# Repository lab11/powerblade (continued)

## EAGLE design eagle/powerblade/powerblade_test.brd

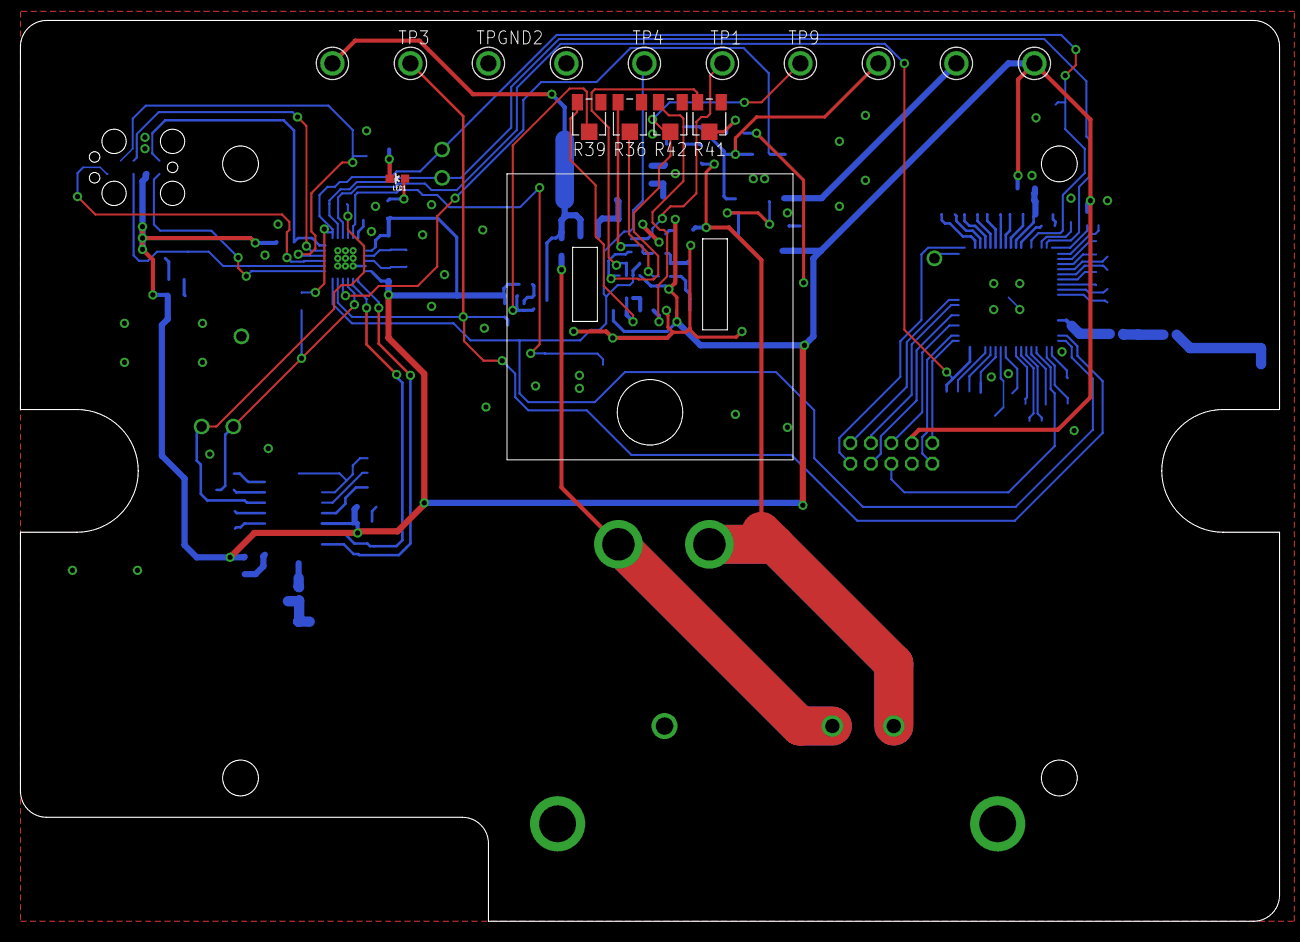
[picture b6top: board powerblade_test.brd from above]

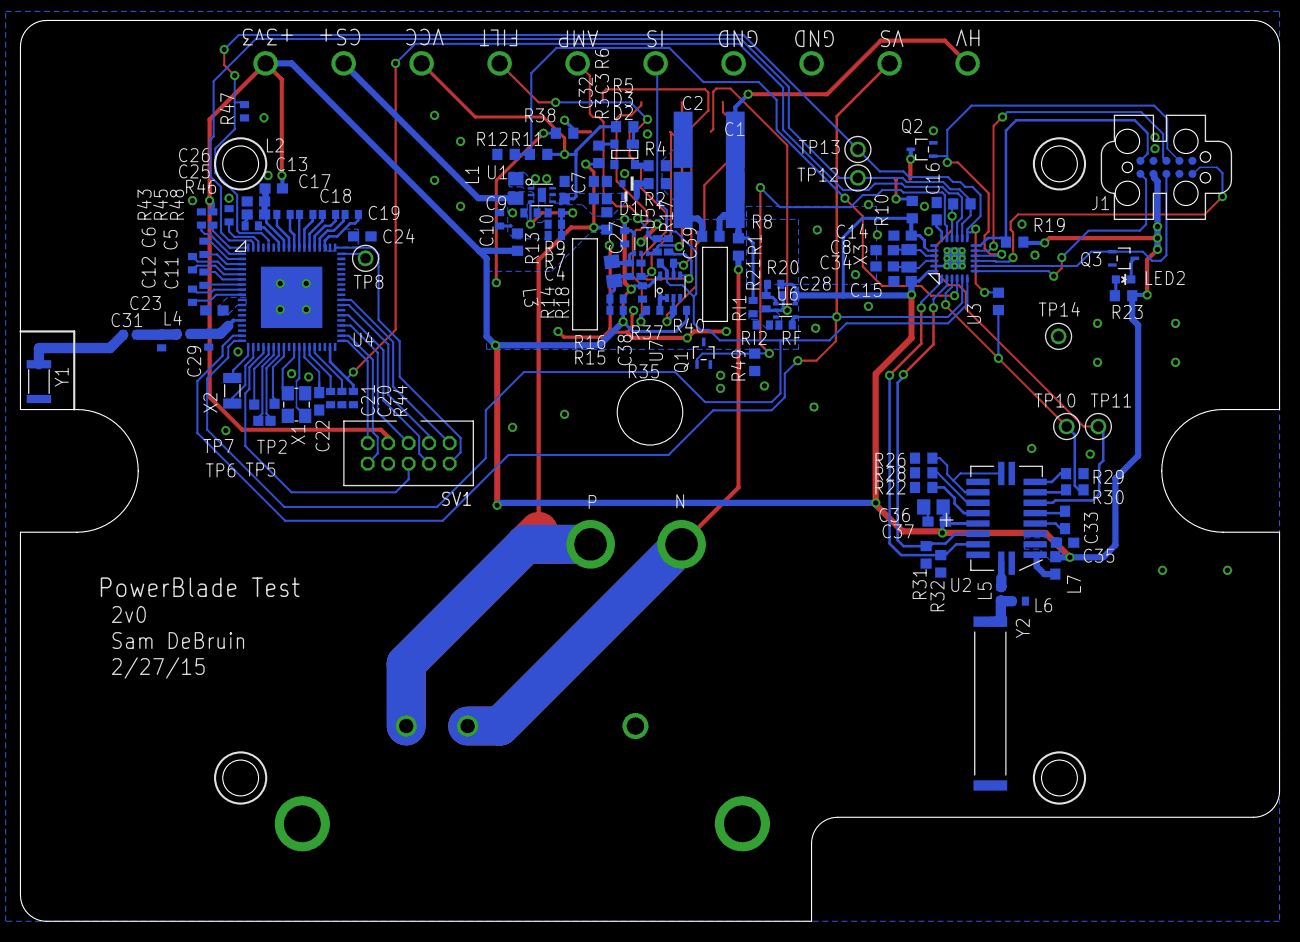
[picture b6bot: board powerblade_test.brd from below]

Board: 2 copper layers, 123.0 x 88.0 mm, 139 parts (123 on the bottom side), 108 nets.

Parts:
ACSLOT: AC_NODIM; AC3_NODIM
C1: 0.033uF 250VAC; C2220K
C2: NP; C2220K
C3, C32: 33uF; C0603
C4: 22pF; C0402
C5, C6, C11, C12, C13, C17, C18, C19, C20, C21: 56nF; C0402
C7: 4.7uF; C0603
C8, C34: 8pF; C0603
C9, C27, C28, C38: 0.1uF; C0402
C10: 4.7uF; C0402
C14, C22, C25: 0.1uF; C0603
C15: 10uF; C0603
C16: 470nF; C0603
C23: 0.47uF; C0603
C24: 0.22uF; C0603
C26: 2.2uF; C0603
C29: 1.2pF; C0402
C30: NP; C0402
C31: 0ohm; C0402
C33: 15nF; C0603
C35: 27pF; C0603
C36: 100pF; C0603
C37: 4.7uF; CPOL-0805
C39: 1.5uF; C0402
CS+: TP_MULT
CS-: TP_MULT
D1: ZENERBZT52; BZT52
D2: DIODE; BAS521
D3: BRIDGE_BGX; TO-253-4
HVS: TP_MULT
J1: JTAG_14PIN_IDC; TC2050-IDC-430
J21: AC_INSW; AC_DC21
L1: 10uH; L0805
L2: 2.2uH; L0603
L3: L0805
L4: 7.5nH; L0402
L5: 10nH; L0402
L6: 100nH; L0402
L7: 100nH; L0603
LED1, LED2: LED-0603
Q1, Q2, Q3: 2SK1829; SC-70-3
R1: 240 0.25W; R0603
R2, R3: 0; R0603
R4, R5, R6, R33, R34: NP; R0603
R7: 560k; R0402
R8: 1M; R0603
R9: 180k; R0402
R10, R23: 120; R0603
R11: 134k 1%; R0603
R12: 67k 1%; R0603
R13: 1 1%; R0603
R14: 200; R0402
R15: NP; R0402
R16, R43: 0; R0402
R17: 20k 1%; R0402
R18: 2.49 1%; R0402
R19, R31, R32, R49: 47k; R0603
R20, R21: 10k 1%; R0402
R22: 270k; R0603
R26, R29: 100k; R0603
R28: 330k; R0603
R30: 4.7k; R0603
R35: 2k 1%; R0402
R36: 20; 3313_POT
R37: 90k 1%; R0402
R38: 3.1k 1%; R0603
R39, R41: 10k; 3313_POT
R40: 100k 1%; R0402
R42: 50k; 3313_POT
R44, R46, R48: 47k; R0402
R45, R47: 12k; R0402
RF: 1.5k 1%; R0402
RI1, RI2: 220k 1%; R0402
RS+: TP_MULT
SV1: MA05-2_KEY
TP1, TP3, TP4, TP9: TP_MULT
TP2, TP5, TP6, TP7: TP_SMD
TP8, TP10, TP11, TP12, TP13, TP14: TP_STD; TP
TPGND1, TPGND2: TP_MULT
U1: TPS62122; WDFN-6
U2: TR1000; SM-20H
U3: MSP430FR5738; VQFN-24
U4: LTC5800; QFN-72
U5, U6: MAX9910; SC70-5
U7: OPA2369; SOT-23-8
X1: ABM8G
X2: ABS07
X3: 32.768kHz; 0805
Y1: UREACH_XTEND
Y2: ANT-916

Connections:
+3V3: C14.1, C15.1, C27.1, C28.1, C35.1, C36.1, C37.+, C38.1, CS-.P$1, J1.P2, L2.1, L7.1, R10.2, R13.2, R15.1, R19.2, R20.2, R23.2, R40.2, R45.2, SV1.7, U2.P3, U2.P16, U3.P20, U3.P24, U5.P5, U6.P5, U7.P8
CNT0: R32.2, U2.P18, U3.P1
CNT1: R31.2, U2.P17, U3.P2
DGND: C27.2, C28.2, C38.2, Q1.P3, R16.1, R18.1, R21.1, R38.1, R39.PW, RI2.1, U5.P2, U6.P2, U7.P4
FLASH_EN: SV1.2, U4.P55
GND: C3.2, C7.2, C8.1, C9.2, C10.2, C14.2, C15.2, C16.1, C20.2, C21.2, C22.2, C23.2, C24.2, C25.2, C26.2, C29.2, C30.2, C32.2, C34.1, C35.2, C36.2, C37.-, D2.A, D3.P3, J1.P9, L6.2, Q1.P2, Q2.P2, Q3.P2, R9.1, R12.1, R22.1, R26.2, R28.1, R29.1, R31.1, R32.1, R43.2, R44.1, R46.1, R47.1, R48.1, R49.1, SV1.8, TP14.P$1, TPGND1.P$1, TPGND2.P$1, U1.P6, U1.PAD, U2.P1, U2.P10, U2.P19, U3.G1, U3.G2, U3.G3, U3.G4, U3.G5, U3.G6, U3.G7, U3.G8, U3.G9, U3.P19, U3.P23, U3.PAD, U4.PAD, X1.P2, X1.P4
IPC_MISO: SV1.5, U4.P40
IPC_MOSI: SV1.4, U4.P42
IPC_SCK: SV1.3, U4.P44
IPC_SS: SV1.1, U4.P45
I_SENSE: R37.2, TP4.P$1, U3.P6, U4.P18, U7.P7
LTC_RRTS: R46.2, U4.P66
LTC_RX: R33.1, R47.2, TP13.P$1, U3.P13, U4.P68
LTC_SLEEP: R44.2, U3.P15, U4.P35
LTC_TCTS: R48.2, U4.P70
LTC_TIME: R45.1, U4.P72
LTC_TX: R34.1, TP12.P$1, U3.P14, U4.P71
METER_EN: Q1.P1, R49.2, U3.P17
N: J21.N, R1.1
unnamed: C34.2, U3.P22, X3.1
unnamed: D1.A, D2.C, R2.2
unnamed: C1.1, C2.1, R2.1, R4.1, R8.2
unnamed: D3.P4, R4.2
unnamed: D3.P1, R5.1
unnamed: D3.P2, R6.2
unnamed: L1.2, U1.P1
unnamed: C5.1, U4.P2
unnamed: C4.1, C9.1, C10.1, CS+.P$1, L1.1, R7.2, R13.1, U1.P2
unnamed: C33.2, U2.P5
unnamed: C4.2, R7.1, R9.2, U1.P3
unnamed: C5.2, U4.P3
unnamed: C6.1, U4.P5
unnamed: L7.2, U2.P2
unnamed: C6.2, U4.P4
unnamed: C11.1, U4.P6
unnamed: C11.2, U4.P7
unnamed: C12.1, U4.P9
unnamed: C12.2, U4.P8
unnamed: C13.1, U4.P64
unnamed: C16.2, U3.P18
unnamed: C13.2, U4.P63
unnamed: C17.1, U4.P61
unnamed: C17.2, U4.P62
unnamed: C18.1, U4.P60
unnamed: C18.2, U4.P59
unnamed: C19.1, U4.P57
unnamed: C19.2, U4.P58
unnamed: C21.1, U4.P31
unnamed: C20.1, U4.P32
unnamed: C25.1, C26.1, L2.2, U4.P65
unnamed: C24.1, U4.P56
unnamed: C23.1, U4.P10
unnamed: C22.1, U4.P30
unnamed: L3.2, R14.1, R15.2, R16.2
unnamed: L3.1, R14.2, U5.P1
unnamed: R17.1, R36.P2, U5.P3
unnamed: R20.1, R21.2, U6.P1
unnamed: RF.1, RI1.2, RI2.2, U6.P3
unnamed: U4.P29, X1.P1
unnamed: U4.P28, X1.P3
unnamed: U4.P20, X2.P2
unnamed: U4.P19, X2.P1
unnamed: C29.1, L4.2, U4.P14
unnamed: C30.1, C31.1, L4.1
unnamed: C31.2, Y1.P1
unnamed: LED1.A, R10.1
unnamed: R22.2, U2.P15
unnamed: R28.2, U2.P14
unnamed: R29.2, U2.P9
unnamed: R30.2, U2.P8
unnamed: LED1.C, Q2.P3
unnamed: C33.1, U2.P6
unnamed: C8.2, U3.P21, X3.2
unnamed: R26.1, U2.P11, U2.P13
unnamed: LED2.A, R23.1
unnamed: LED2.C, Q3.P3
unnamed: TP8.P$1, U4.P54
unnamed: C39.1, R17.2, TP1.P$1, U5.P4
unnamed: L5.2, U2.P20
unnamed: L5.1, L6.1, Y2.P1
unnamed: R18.2, R36.PW
unnamed: R37.1, R41.P2, U7.P6
unnamed: C39.2, R42.PW, TP9.P$1, U7.P5
unnamed: R35.1, U7.P1, U7.P2
unnamed: R38.2, R41.PW
unnamed: R39.P2, R40.1, U7.P3
unnamed: R35.2, R42.P2
unnamed: TP7.P$1, U4.P23
unnamed: TP6.P$1, U4.P24
unnamed: TP5.P$1, U4.P25
unnamed: TP2.P$1, U4.P26
unnamed: R43.1, U4.P1
NRST: SV1.6, U4.P22
P: J21.L, R3.1, R6.1
RST: J1.P10, R19.1, U3.P12
RXDATA: R34.2, TP11.P$1, U2.P7, U3.P16
TCK: J1.P7, Q2.P1, U3.P10
TDI: J1.P3, Q3.P1, U3.P8
TDO: J1.P1, U3.P7
TEST: J1.P8, U3.P11
TMS: J1.P5, U3.P9
TXMOD: R30.1, R33.2, TP10.P$1, U3.P3
UC_RX: SV1.10, U4.P38
UC_TX: SV1.9, U4.P37
VCC: C3.1, C7.1, C32.1, D1.C, R3.2, R5.2, R11.2, RS+.P$1, U1.P4, U1.P5
VCC_SENSE: R11.1, R12.2, U3.P4
VTEST: C1.2, C2.2, HVS.P$1, R1.2, R8.1, RI1.1
V_SENSE: RF.2, TP3.P$1, U3.P5, U4.P17, U6.P4

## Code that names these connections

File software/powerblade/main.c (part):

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
#define I_PIN		BIT3

#define LED1_PIN	BIT7
#define LED2_PIN	BIT2
#define LED3_PIN	BIT6
#define LED1_DIR	P1DIR
#define LED2_DIR	P2DIR
#define LED3_DIR	P1DIR
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    P2REN = 0xFF;

    // Set up LEDs as outputs
//    LED1_DIR |= LED1_PIN;
//    LED2_DIR |= LED2_PIN;
//    LED3_DIR |= LED3_PIN;

    // Set up RX input
    P2DIR &= ~RX_PIN;							// Set RX to input
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//    while(1) {
//    	volatile unsigned long i = 0;
//
//    	LED1_OUT ^= LED1_PIN;
//
//    	for(i = 1000000; i > 0; i--);
//    }
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	TB0CCTL0 &= ~CCIFG;

	// Indicate RX
	//LED2_OUT ^= LED2_PIN;

	switch(rf_mode) {
	case rf_idle:
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
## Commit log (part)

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2016-10-10 added push to db
2016-10-10 made uploads async
2016-10-10 changed to foreach
2016-10-10 fixed small error in sql upload
2016-10-11 minor changes
2016-10-12 dat_powerblade_2 table actually has flags column
2016-10-17 status script with email appears to work
2016-10-17 flags now includes software version number
2016-10-17 other updates
2016-10-17 fixed error in readme
2016-10-17 fixed test error
2016-10-17 fixed email formatting
2016-10-18 major updates
2016-10-18 fixed errors
2016-10-18 added extra lines in header
2016-10-18 fixed error in finding stuff in list
2016-10-18 added writes on errors
2016-10-18 no errors no email
2016-10-18 added better error output
2016-10-18 exit if no prompt
2016-10-18 formatting on datetime
2016-10-18 only write error file ony shortrun
2016-10-18 smaller space after gateway
2016-10-18 added a second email subject
2016-10-18 added software version 2v2v1
2016-10-18 added flags to powerblade adv listener
2016-10-20 fixed some errors and changed logpath
2016-10-20 changed all error to status
2016-10-20 fixed errors in read file
2016-11-17 moved conv data (plotting for powerblade accuracy issue) to powerblade repo
2016-11-17 user friendly readme
2016-11-17 readme formatting
2016-11-21 prep work for extended measurements
2016-11-22 temp measurements
2016-11-28 working with env PB_DATA
2016-11-28 finished making updates
2016-11-28 updated and fixed errors
2016-11-29 moved wattsup script to a more reasonable folder
2016-11-29 data check works with missing and clear features
2016-11-29 added data output stuff
2016-11-30 cleaned up printout in datacheck
2016-11-30 fixed two errors with sql
2016-11-30 maxDiff output file ignored
2016-11-30 added string versions of ip
2016-11-30 final version
2016-11-30 changed to _power
2016-12-02 measurement allows for overwrite
2016-12-06 data printing almost done for sorted maxdiff measurements
2016-12-06 hoping this fixes the crontab issue in node
2016-12-07 finished first draft of accuracy plots
2016-12-07 added location to powerblade status
2016-12-08 added node-cron to package
2016-12-08 looking for different error
2016-12-09 turned down status frequency
2016-12-12 changed frequency on status script
2016-12-12 wattsup script can replace the file
2016-12-12 data check no longer proceeds if there are missing elements
2016-12-12 specify device seperately in measurements
2016-12-12 data_check doesnt generate reports for partial checks
2016-12-13 added explicit connection in status
2016-12-13 fixed error
2016-12-14 moved data to shed-data
2016-12-14 changed default count to 50
2016-12-20 measurements runs data check
2016-12-22 added location to powerblade lookup upload
2017-01-04 measurements script outputs seq num
2017-01-04 cleaned up the print statements in calibrate
2017-01-06 changed the way calibrate works with inputs
2017-01-30 started the commissioning script
2017-01-31 work on commission script
2017-02-06 commission script uploads to aws when done
2017-02-07 Added check for device id
2017-02-11 removed some old files and folders
2017-02-11 added check if power is in right bound
2017-02-12 new way of splitting
2017-02-12 more error output
2017-02-12 automatically setting to 100 works, correct error checking in msp430 programming
2017-02-12 added the -n flag
2017-02-21 created working (started) copy of create_view
2017-02-27 added location to upload_status_form
2017-02-27 added sql status v2
2017-02-27 updated to sql status
2017-03-07 updated upload status form
2017-03-07 updated sql status to include blink and light
2017-03-07 check time when script starts
2017-03-08 plot program basic funciton working
2017-03-09 added the most_recent_powerblades subset of inf_pb_lookup
2017-03-09 energy stuff starting to work
2017-03-10 works for month-day
2017-03-11 better printing
2017-03-11 final edit - devices no longer print ok
2017-03-11 different th for ligeiro
2017-03-11 final change
2017-03-11 changed thold for countTh
2017-03-11 dont print the ok symbol
2017-03-14 total energy is starting to work
2017-03-21 changed energy queries
2017-03-21 added queries for energy breakdown
2017-03-21 updated scratchpad
2017-03-21 added first versions of loc pdfs
2017-03-22 added plt printout to plot file
2017-03-23 starting work in blees and ligeiro
2017-03-23 plot works for blees and ligeiro
2017-03-23 updated sql scripts
2017-03-23 downsampled plotting so it doesnt take as long
2017-03-24 cleaned up v2 email
2017-03-24 updated view
2017-03-24 starting to add blink
2017-03-24 updated to msp430 software version 2.3.0 where watthours is now stored in non volatile memory (stupid)
2017-03-25 added wave to commissioning
2017-03-25 switched to active list
2017-03-25 added cdf stuff to plot data
2017-03-25 added gnd truth table
2017-03-26 switched to printEnergy format and added combine script
2017-03-26 added remTime format to everything
2017-03-27 cleaned up folder
2017-03-27 updates to all
2017-03-27 updated database model
2017-03-27 added status model
2017-03-28 general updates
2017-03-28 added the info tag and separated the maxpower and energy stuff
2017-03-29 added the day resets thing
2017-03-29 altered active_devices to have category and type
2017-03-29 added blees and ligeiro to stats
2017-03-29 added final results table
2017-03-29 breakdown combine works (results)
2017-03-31 updated scripts and moved data to shed
2017-03-31 updates to scripts to support final graphs
2017-03-31 create view has dev_actResets
2017-03-31 various changes
2017-04-02 minor update to stats
2017-04-02 added special ligeiro script
2017-04-03 fixed duration days and added more columns to final gnd truth
2017-04-03 fixed comment
2017-04-04 basic updates to plotting
2017-04-04 added stats incl stdev to data_check
2017-04-04 basic edits to scratchpad and statistics
2017-04-05 minor changes throughout
2017-04-07 added cat breakdown stuff for boxplot
2017-04-07 added brads ligeiro query
2017-04-08 small change to create view
2017-04-08 added ligeiro query for brad
2017-04-08 plot data is in sorry shape, but it works with the l0 tables
2017-04-08 added boxplot plt file
2017-04-08 added boxplot into plot_data script
2017-04-08 added the sequence index
2017-04-10 added seq index
2017-04-10 system works again (i think) after loc0 stuff
2017-04-17 updates to measurements
2017-04-17 changed to dat_pb_config
2017-04-19 added occ query
2017-04-19 change to valid_lights and blinks
2017-04-19 finished updating to valid tables
2017-04-19 removed the perm stuff
2017-04-19 renamed ebreakdown table to loc1_ebreakdown
2017-04-19 changes to scratchpad
2017-04-19 cleaned up loc0 avgPoewr
2017-04-19 cleaned up loc0 stuff in plot
2017-04-19 updated seq to use seq_powerblade not temp_powerblade
2017-04-19 cleaned up and added commetns
2017-04-19 renamed final ss table
2017-04-19 cleaned up create_tables script
2017-04-19 cleaned up upload status form
2017-04-19 cleaned up occupancy script
2017-04-19 cleaned up statistics (archived old copy)
2017-04-19 cleaned up create view v2 script - v1 left alone
2017-04-19 cleaned up loc0
2017-04-20 plot data supports rooms
2017-04-24 calc deltas works for calc'ing deltas
2017-04-24 only calc deltas on categories for id
2017-04-25 created blink output
2017-04-25 added 4-part index on dev power time seq
2017-04-25 added deltas table to create_tables
2017-04-25 calc deltas set up for location 3
2017-04-25 switched from valid_devices_2
2017-04-25 added dev id script
2017-04-27 added new table
2017-04-27 calc deltas set up for loc 0
2017-04-27 added calc vectors script
2017-04-27 added delta and vector views
2017-04-27 created script for generating arff files
2017-04-27 cleaned up device ID
2017-04-27 occ set up for l0
2017-04-28 occ ready for l3
2017-04-28 occ set up for l5
2017-04-28 downsample changed to 3600, set up for l8 (old data deleted)
2017-04-28 occ set up for l9
2017-04-29 occ set up for the rest of 3
2017-04-30 created new user for josh in database
2017-04-30 ignoring pdf files
2017-04-30 added the dat_occ tables
2017-04-30 added the dat_occ stuff to stats
2017-04-30 minor changes to occ plot formatting
2017-05-02 added fault difference file
2017-05-03 blink asks to save to final
2017-05-03 the blink queries not convert utc to detroit time, but the rest of the queries dont do that yet (probably never will)
2017-05-04 updated gitignore
2017-05-09 changed x on sql files
2017-05-12 added fault detection stuff
2017-05-13 added occupancy and vector calc to calc_deltas
2017-05-14 occupancy in classification basically works
2017-05-15 testweka app pretty much works for testing all the combinations for device id
2017-05-16 added latex-style table printout to testweka
2017-05-17 updated calc deltas to cinlude veel not working
2017-05-18 added the idle savings potential stuff to plot data
2017-05-19 fixed blink plotting
2017-05-19 added inter dev corr
2017-05-19 final work on fault detection
2017-05-21 overhaul of testweka - using temp tables and addition of bayesian stuff
2017-05-21 files part of move to temp tables for testweka
2017-05-23 a bunch of other probability stuff works
2017-06-05 better device category stuff
2018-07-28 Script to download Voltage and Current samples
    Super manual at this point, with calibration parameters hardcoded in the
    `collect_samples.js` file.
2018-12-14 add better assembly files
2018-12-17 expand on readme
2019-01-15 Update sample collection script
2019-01-25 Update README and add example config file.
2019-01-25 Add 'wait for keypress' to sample collection
2019-05-08 Move accumulate to end
2019-05-09 increase circular buffer size
2019-05-10 Transferring waveform from MSP to nRF each second
    This code still has a lot of debugging artifacts and tests in it
    To get this working we needed to:
    * Increase baudrate from MSP to nRF
    * Keep baudrate the same from nRF to MSP
    * Increase priority of the nRF UART RX interrupt
    * Split nRF RX interrupt into top-half and bottom-half handlers
2019-05-11 Waveform collection connection firmware
2019-05-14 Filter and calibration working
    Mixed results - power factor seems off, possibly due to unfiltered
    voltage and filtered voltage mismatch
    Measurements seem accurate
2019-05-14 Fix big endian printing bug for curoff, pscale
2019-05-14 Waveform collection script!
2019-05-15 fix indentation
2019-05-15 well that would do it
2019-05-17 Waveform visualization can now save the waveforms
2019-05-20 MSP software update to version 4
    Decided that that changes we made in this code were enough to warrant it
2019-05-22 Port powerblade msp code to linux c
    Pretty much straight up copy of filter code, calibration loops.
2019-05-22 fix overflow, save to file
2019-05-22 add offsets to plotting
2019-05-23 Recreated filtering, doesn't work that well
2019-05-28 switched to fixed point
2019-05-30 Successfully implement EMA filter.
    Sample collection still works, but waveform collection is returning all
    zeros.
2019-07-02 fix measurements script
2019-07-11 Allow empty queue, prevent repeated waveform
    Don't fill queue if empty, keep track of most recent waveform until
    another is found.
2019-07-11 Use common data format for waveform services
    2 bytes: adv_len
    24 bytes: adv_data
    2 bytes: waveform_len
    168 bytes: waveform_data
2019-07-12 Decrease sensitivity for "uniqueness" metric
    Add in some minimum power requirements to prevent constant unique
    waveforms for when devices are off.
2019-07-16 notify 0 when no waveforms available
2019-07-16 waveform visualization wait for keypress before exit
2019-09-11 powerblade fft on nrf52840
2019-09-12 send integrated signal too
2019-12-05 start chroma load emulator calibration script
2019-12-05 add simple chroma library, works
2019-12-06 Sweep pf/p, still need to iron out kinks
2019-12-07 clean up control flow a little
2019-12-09 POW->CURR Fixes #12
